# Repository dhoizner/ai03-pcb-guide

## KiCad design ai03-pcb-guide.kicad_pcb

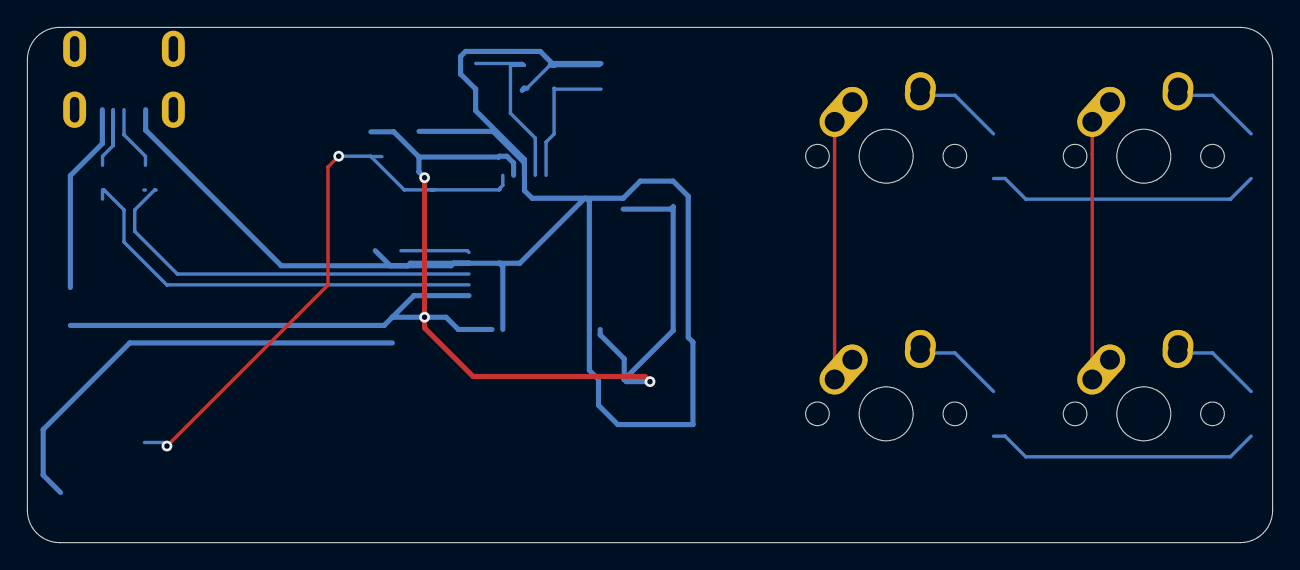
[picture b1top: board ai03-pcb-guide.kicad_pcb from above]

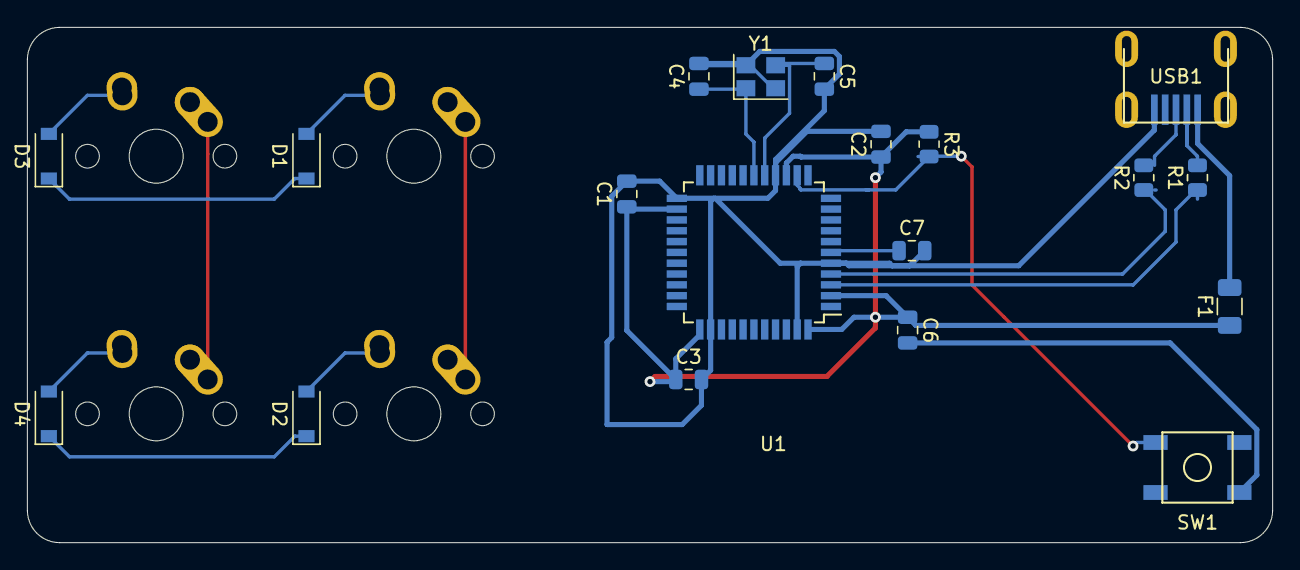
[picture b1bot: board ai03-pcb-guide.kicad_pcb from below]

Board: 2 copper layers, 92.1 x 38.1 mm, 23 parts (19 on the bottom side), 19 nets.

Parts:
C1, C2, C3: 0.1uF; C_0805_2012Metric
C4, C5: 22pF; C_0805_2012Metric
C6: 10uF; C_0805_2012Metric
C7: 1uF; C_0805_2012Metric
D1, D2, D3, D4: D_Small; D_SOD-123
F1: 500mA; Fuse_1206_3216Metric
MX1, MX2, MX3, MX4: MX-NoLED; MX-1U-NoLED
R1, R2: 22; R_0805_2012Metric
R3: 10k; R_0805_2012Metric
SW1: SW_Push; SKQG-1155865
U1: ATmega32U4-AU; TQFP-44_10x10mm_P0.8mm
USB1: Molex-0548190589
Y1: 16MHz; Crystal_SMD_3225-4Pin_3.2x2.5mm

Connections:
+5V: C1.1, C2.1, C3.1, C6.1, F1.1, R3.1, U1.2, U1.7, U1.14, U1.24, U1.34, U1.44
COL0: MX1.1, MX2.1
COL1: MX3.1, MX4.1
D+: R2.2, USB1.3
D-: R1.2, USB1.4
GND: C1.2, C2.2, C3.2, C4.2, C5.2, C6.2, C7.2, SW1.1, U1.5, U1.15, U1.23, U1.35, U1.43, USB1.1, Y1.2, Y1.4
unnamed: C4.1, U1.17, Y1.1
unnamed: C5.1, U1.16, Y1.3
unnamed: C7.1, U1.6
unnamed: D1.2, MX1.2
unnamed: D2.2, MX2.2
unnamed: D3.2, MX3.2
unnamed: D4.2, MX4.2
unnamed: R1.1, U1.3
unnamed: R2.1, U1.4
unnamed: R3.2, SW1.2, U1.13
ROW0: D1.1, D3.1
ROW1: D2.1, D4.1
VCC: F1.2, USB1.5

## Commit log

2021-07-13 initialize project
2021-07-13 add hybrid footprint and parts submodules
2021-07-13 add symbol and footprint libraries to project
2021-07-13 complete mcu zone
2021-07-13 schematic complete
2021-07-14 remove random cache.lib file
2021-07-14 fuck.
